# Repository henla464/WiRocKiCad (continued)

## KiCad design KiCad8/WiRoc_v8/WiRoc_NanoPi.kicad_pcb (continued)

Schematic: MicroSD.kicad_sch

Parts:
C30: 10uF/6.3V; C_0402_1005Metric
J3: Micro_SD_Card_Det1; TF-SMD_TF-018B-H15
R22: 33R; R_0402_1005Metric
R23, R24: 47K; R_0402_1005Metric
RV1, RV2, RV3, RV4, RV5, RV6, RV7, RV8: AVRL101A1R1NTB; R_0402_1005Metric

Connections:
GND: C30.1, J3.6 (VSS), J3.10 (SHIELD), RV1.2, RV2.2, RV3.2, RV4.2, RV5.2, RV6.2, RV7.2, RV8.2; also elsewhere on the board
unnamed: J3.5 (CLK), R22.2, RV6.1
SDC0-CLK: R22.1; also elsewhere on the board
SDC0-CMD: J3.3 (CMD), R23.1, RV1.1; also elsewhere on the board
SDC0-D0: J3.7 (DAT0), RV5.1; also elsewhere on the board
SDC0-D1: J3.8 (DAT1), RV4.1; also elsewhere on the board
SDC0-D2: J3.1 (DAT2), RV8.1; also elsewhere on the board
SDC0-D3: J3.2 (DAT3/CD), RV7.1; also elsewhere on the board
SDC0-DET: J3.9 (DET), R24.1, RV3.1; also elsewhere on the board
VDD_SYS_3.3V: C30.2, J3.4 (VDD), R23.2, R24.2, RV2.1; also elsewhere on the board

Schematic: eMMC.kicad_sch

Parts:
C32, C35, C80, C87, C88: 100nF; C_0402_1005Metric
C33, C34, C86: 1uF; C_0402_1005Metric
R26: 10K; R_0402_1005Metric
U14: KLM8G1WEPD-B031; MICRON_EMMC_153

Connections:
GND: C32.2, C33.2, C34.2, C35.2, C80.2, C86.2, C87.2, C88.2, U14.A6 (Vss), U14.C4 (Vss), U14.D4 (NC33), U14.E7 (Vss), U14.G5 (Vss), U14.H10 (Vss), U14.J5 (Vss), U14.K8 (Vss), U14.N2 (Vss), U14.N5 (Vss), U14.P2 (NC102), U14.P4 (Vss), U14.P6 (Vss), U14.P8 (NC103); also elsewhere on the board
unnamed: C32.1, C33.1, U14.C1 (NC19), U14.C2 (VDDI)
VDD_SYS_3.3V: C34.1, C35.1, C80.1, C86.1, C87.1, C88.1, R26.1, U14.C6 (VDD), U14.E6 (VDDF), U14.F5 (VDDF), U14.J10 (VDDF), U14.K9 (VDDF), U14.M4 (VDD), U14.N4 (VDD), U14.P3 (VDD), U14.P5 (VDD); also elsewhere on the board
eMMC-CLK: U14.M6 (CLK); also elsewhere on the board
eMMC-CMD: R26.2, U14.M5 (CMD); also elsewhere on the board
eMMC-D0: U14.A3 (DAT0); also elsewhere on the board
eMMC-D1: U14.A4 (DAT1); also elsewhere on the board
eMMC-D2: U14.A5 (DAT2); also elsewhere on the board
eMMC-D3: U14.B1 (NC10), U14.B2 (DAT3); also elsewhere on the board
eMMC-D4: U14.A2 (NC2), U14.B3 (DAT4); also elsewhere on the board
eMMC-D5: U14.B4 (DAT5), U14.C3 (NC20), U14.D1 (NC30), U14.D2 (NC31); also elsewhere on the board
eMMC-D6: U14.B5 (DAT6), U14.C5 (NC21); also elsewhere on the board
eMMC-D7: U14.A7 (RFU1), U14.B6 (DAT7); also elsewhere on the board
eMMC-RST: U14.K5 (RSTN); also elsewhere on the board

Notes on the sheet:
* Connected to simplify fanout from the eMMC chip

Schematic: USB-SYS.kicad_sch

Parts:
C31, C37, C39, C42, C43: 100nF; C_0402_1005Metric
C36: 1uF; C_0402_1005Metric
C38, C44: 4.7uF; C_0402_1005Metric
C40, C41: 18pF; C_0402_1005Metric
R27: 47K; R_0402_1005Metric
R28: 100K; R_0402_1005Metric
R29, R30, R31, R32: 10K; R_0402_1005Metric
R43: 0R; R_0402_1005Metric
U11: BGA-347_21x21_14.0x14.0mm
U13: SGM803-RXN3L; SOT-23-3
Y2: 24MHz/18pF; Crystal_SMD_2520-4Pin_2.5x2.0mm

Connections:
AP-RESET: C42.1, R29.2, U11.V6 (RESET), U13.2 (/RESET)
GND: C31.2, C36.1, C37.2, C38.2, C39.1, C40.1, C41.1, C42.2, C43.2, C44.2, U11.H8 (GND_TV), U11.M5 (HGND), U11.U3 (AGND), U13.1 (GND), Y2.2, Y2.4; also elsewhere on the board
GPIOL6/CPUX-VSET: U11.T4 (PL6/S_JTAG_DO/S_PL_EINT6); also elsewhere on the board
GPIOL8/PWR-STB: U11.T2 (PL8/S_PL_EINT8); also elsewhere on the board
GPIOL9/PWR-DRAM: U11.M6 (PL9/S_PL_EINT9); also elsewhere on the board
GPIOL10/PWR-LED: U11.V2 (PL10/S_PWM/S_PL_EINT10); also elsewhere on the board
LORARS: U11.U2 (PL11/S_CIR_RX/S_PL_EINT11); also elsewhere on the board
unnamed: R30.1, U11.R1 (PL3/S_UART_RX/S_PL_EINT3)
unnamed: R31.1, U11.N2 (PL4/S_JTAG_MS/S_PL_EINT4)
unnamed: C36.2, U11.W3 (MBIAS)
unnamed: R28.2, U11.AA5 (KEYADC)
unnamed: R27.2, U11.AA6 (NMI)
unnamed: R32.1, U11.W6 (UBOOT)
unnamed: C39.2, R43.1, U11.N3 (VCC_PLL)
unnamed: C38.1, U11.H11 (VDD_EFUSEBP)
USBHost-DM1: U11.A8 (USB_DM2); also elsewhere on the board
USBHost-DM2: U11.B9 (USB_DM3); also elsewhere on the board
USBHost-DP1: U11.A7 (USB_DP2); also elsewhere on the board
USBHost-DP2: U11.B8 (USB_DP3); also elsewhere on the board
VDD1V1-EPHY: U11.F8 (EPHY_VDD); also elsewhere on the board
VDD-CPUS: C44.1, U11.M4 (RTC_VIO); also elsewhere on the board
VDD_SYS_3.3V: C31.1, C37.1, C43.1, R27.1, R28.1, R29.1, R30.2, R31.2, R32.2, R43.2, U11.G7 (EPHY_VCC), U11.G9 (V33_TV), U11.G10 (VDD_EFUSE), U11.G11 (VCC-USB), U11.J6 (HVCC), U11.K6 (VCC_RTC), U11.V3 (AVCC), U13.3 (Vin); also elsewhere on the board
X24MI: C40.2, U11.K2 (X24MIN), Y2.1
X24MO: C41.2, U11.K1 (X24MOUT), Y2.3

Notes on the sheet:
ZeroPi uses a ferrite bead
Close to IC
Note: ZeroPi used 22pF capacitor and crystal has value "XTAL-2520-4P"
wifi clock,shouldn't be needed
WIFI (enable)

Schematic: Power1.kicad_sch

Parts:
C93, C95, C96: 10uF/6.3V; C_0402_1005Metric
C94: 22pF; C_0402_1005Metric
L6: DFE252010P-1R0M=P2; L_1008_2520Metric
Q1: L2N7002WT1G; SOT-323_SC-70
R50: 10K/1%; R_0402_1005Metric
R53: 12K/1%; R_0402_1005Metric
R54: 30K/1%; R_0402_1005Metric
R55: 10K; R_0402_1005Metric
U18: MP2143DJ; TSOT-23-8-Thinner-Pads

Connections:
GND: C93.2, C95.2, C96.2, Q1.2 (S), R53.1, U18.4 (GND), U18.6 (GND1); also elsewhere on the board
GPIOL6/CPUX-VSET: Q1.1 (G), R55.1; also elsewhere on the board
GPIOL8/PWR-STB: U18.8 (EN); also elsewhere on the board
unnamed: Q1.3 (D), R54.1
unnamed: C94.2, R50.1, R53.2, R54.2, U18.7 (FB)
unnamed: L6.1, U18.3 (SW)
VDD-CPUFB: C94.1, R50.2; also elsewhere on the board
VDD-CPUX: C95.1, C96.1, L6.2, U18.5 (OUT); also elsewhere on the board
VDD_5V: C93.1, U18.2 (VIN); also elsewhere on the board
VDD_SYS_3.3V: R55.2; also elsewhere on the board

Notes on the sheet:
GPIOL6/CPUX-VSET = 0, VDD-CPUX=1.1V GPIOL6/CPUX-VSET = 1, VDD-CPUX=1.3V
1.1V/1.3V/3A
Vfb=0.6V

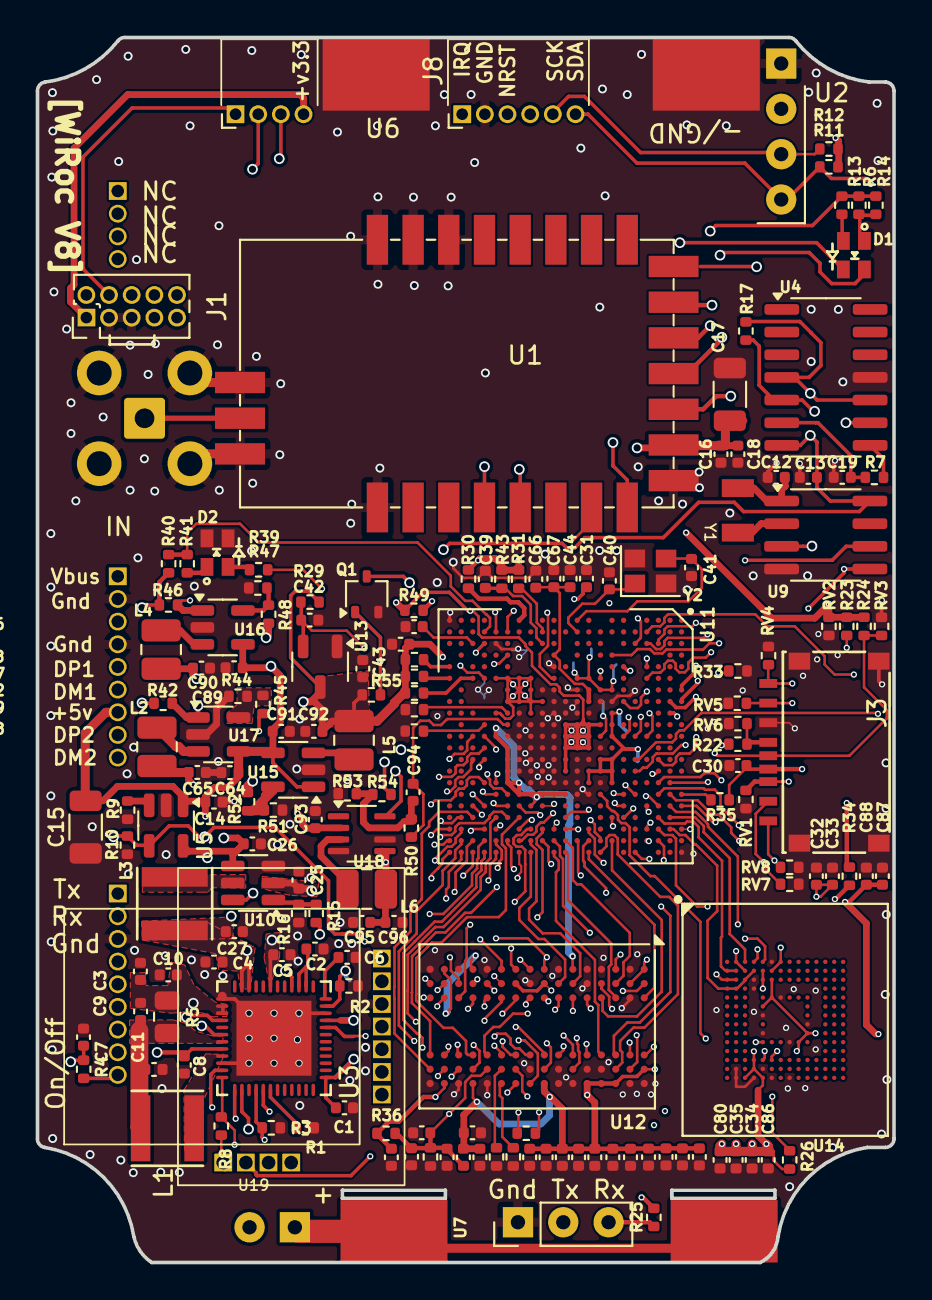
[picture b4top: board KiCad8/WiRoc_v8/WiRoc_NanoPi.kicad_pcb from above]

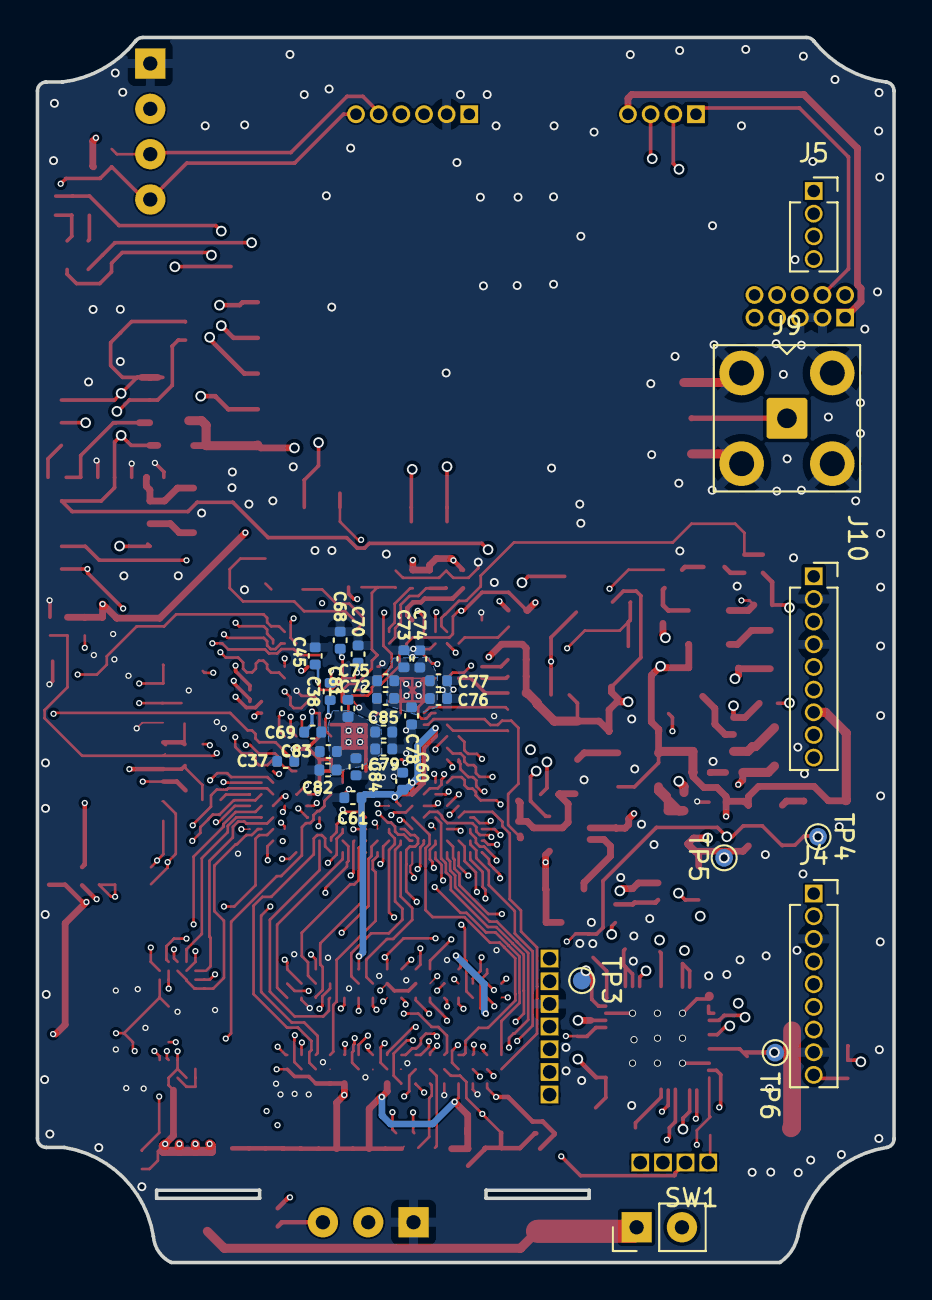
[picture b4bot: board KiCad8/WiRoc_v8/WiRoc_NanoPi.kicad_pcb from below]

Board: 6 copper layers, 48.0 x 68.7 mm, 197 parts (30 on the bottom side), 178 nets.

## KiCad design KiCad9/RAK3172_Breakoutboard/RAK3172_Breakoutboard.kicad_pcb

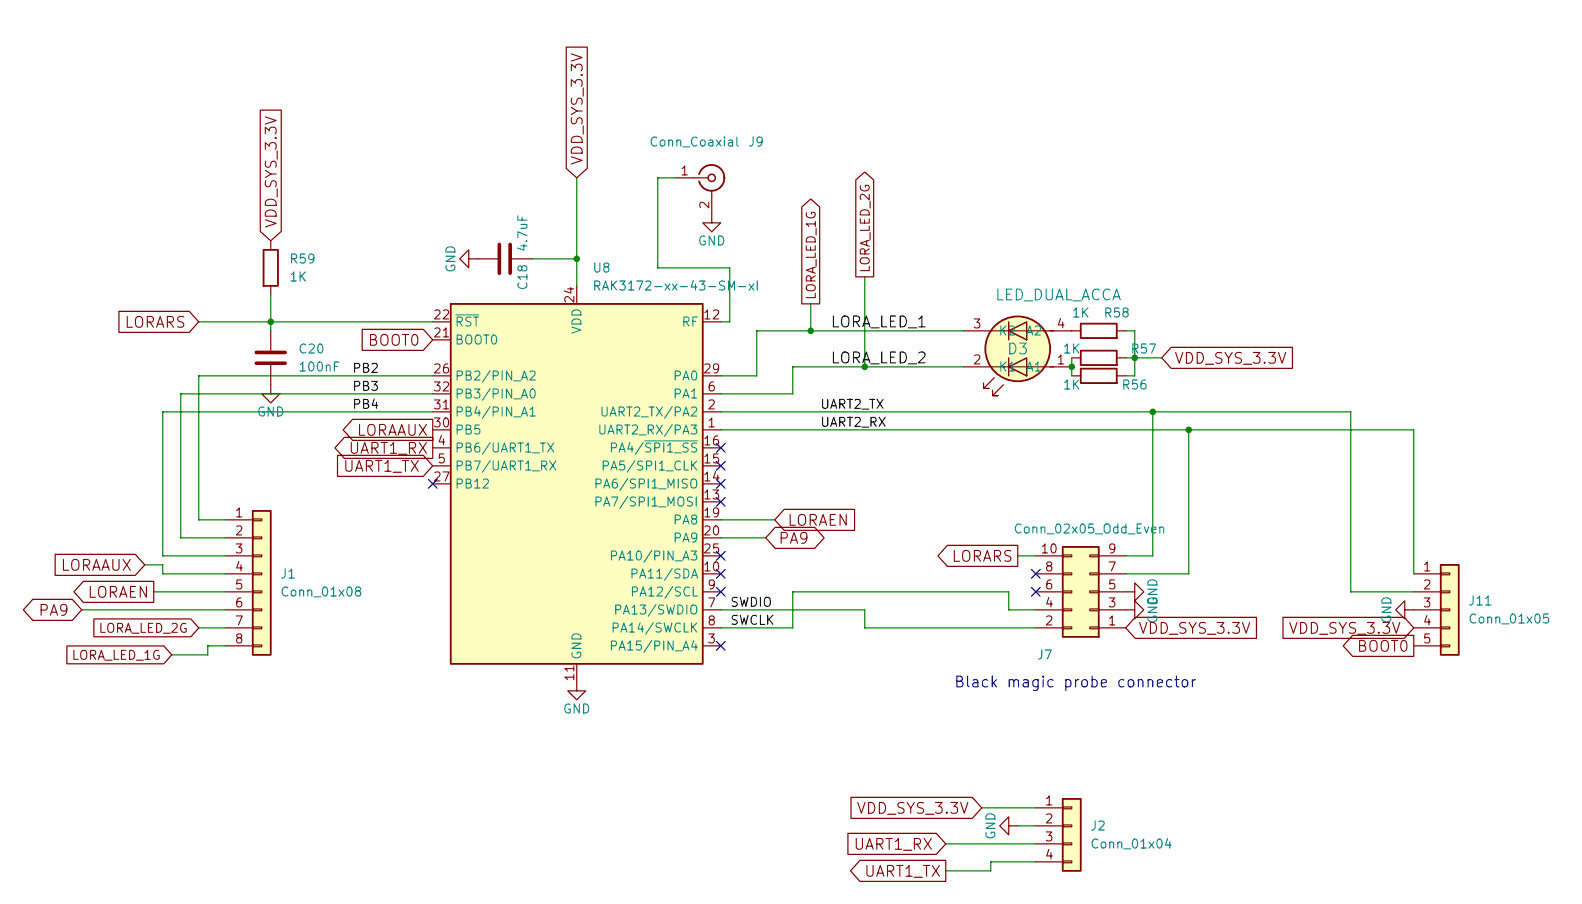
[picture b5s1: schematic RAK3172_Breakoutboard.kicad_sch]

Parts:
C18: 4.7uF; C_0603_1608Metric; ManufacturerPartNumber CL10A475KO8NNNC; LCSC Part # C19666
C20: 100nF; C_0402_1005Metric
D3: LED_DUAL_ACCA; LED_Dual_1.7_1.6; ManufacturerPartNumber HL-PCB-1617S9FH203BC; LCSC Part # C513363
J1: Conn_01x08; PinHeader_1x08_P2.54mm_Vertical
J2: Conn_01x04; PinHeader_1x04_P2.54mm_Vertical
J7: Conn_02x05_Odd_Even; PinHeader_2x05_P1.27mm_Vertical
J9: Conn_Coaxial; SMA_Amphenol_901-143_Horizontal
J11: Conn_01x05; PinHeader_1x05_P2.54mm_Vertical
R56, R57, R58: 1K; R_0603_1608Metric; ManufacturerPartNumber 0603WAJ0102T5E; LCSC Part # C21190
R59: 1K; R_0603_1608Metric
U8: RAK3172-xx-43-SM-xI; RAK3172

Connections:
/PB2: J1.1, U8.26 (PB2/PIN_A2)
/PB3: J1.2, U8.32 (PB3/PIN_A0)
/PB4: J1.3, U8.31 (PB4/PIN_A1)
/SWCLK: J7.4, U8.8 (PA14/SWCLK)
/SWDIO: J7.2, U8.7 (PA13/SWDIO)
/UART2_RX: J7.7, J11.1, U8.1 (UART2_RX/PA3)
/UART2_TX: J7.9, J11.2, U8.2 (UART2_TX/PA2)
BOOT0: J11.5, U8.21 (BOOT0)
GND: C18.2, C20.2, J2.2, J7.3, J7.5, J9.2 (Ext), J11.3, U8.11 (GND), U8.17 (GND), U8.18 (GND), U8.23 (GND), U8.28 (GND)
LORAAUX: J1.4, U8.30 (PB5)
LORAEN: J1.5, U8.19 (PA8)
LORARS: C20.1, J7.10, R59.2, U8.22 (~RST)
LORA_LED_1G: D3.3 (K2), J1.8, U8.29 (PA0)
LORA_LED_2G: D3.2 (K1), J1.7, U8.6 (PA1)
unnamed: D3.1 (A1), R56.1, R57.1
unnamed: D3.4 (A2), R58.1
unnamed: J9.1 (In), U8.12 (RF)
PA9: J1.6, U8.20 (PA9)
UART1_RX: J2.3, U8.4 (PB6/UART1_TX)
UART1_TX: J2.4, U8.5 (PB7/UART1_RX)
VDD_SYS_3.3V: C18.1, J2.1, J7.1, J11.4, R56.2, R57.2, R58.2, R59.1, U8.24 (VDD)

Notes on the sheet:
Black magic probe connector

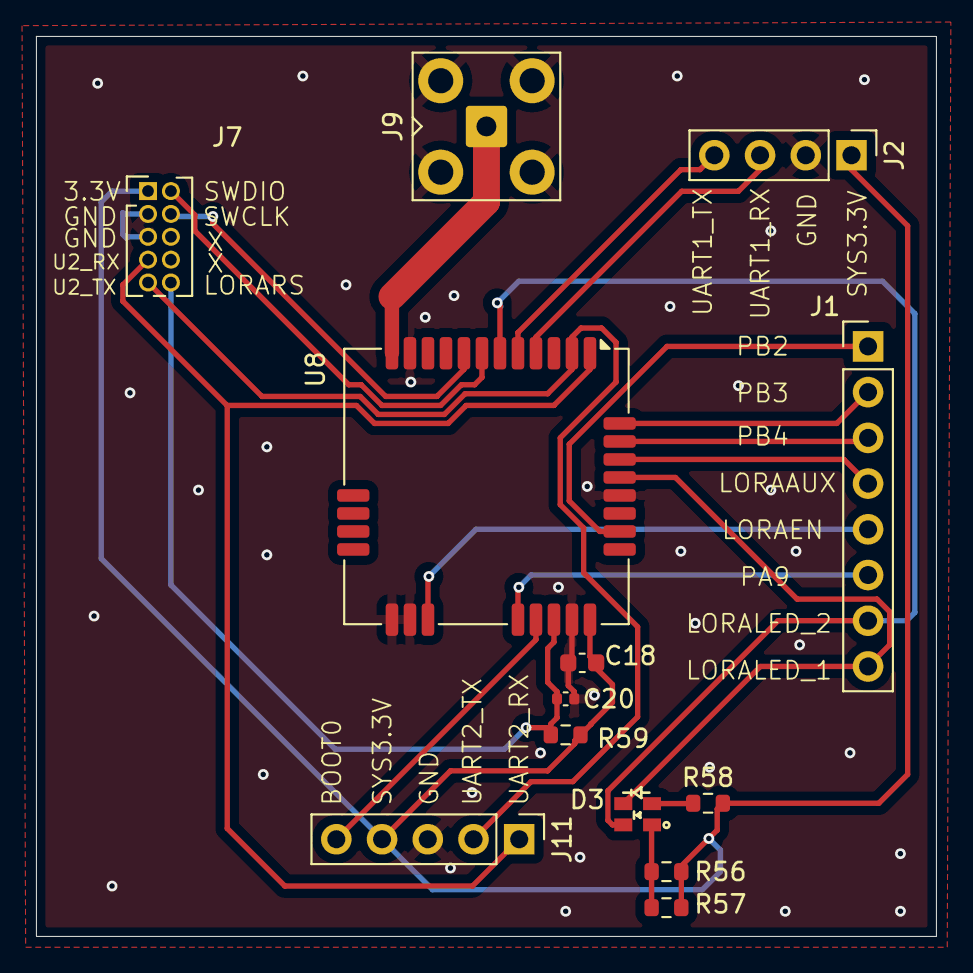
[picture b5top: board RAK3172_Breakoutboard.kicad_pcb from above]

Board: 2 copper layers, 50.0 x 50.0 mm, 13 parts (0 on the bottom side), 21 nets.

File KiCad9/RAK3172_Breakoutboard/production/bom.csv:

Designator,Footprint,Quantity,Value,LCSC Part #
C18,0603,1,4.7uF,C19666
C20,0402,1,100nF,
D3,LED_Dual_1.7_1.6,1,LED_DUAL_ACCA,C513363
J1,PinHeader_1x08_P2.54mm_Vertical,1,Conn_01x08,
J11,PinHeader_1x05_P2.54mm_Vertical,1,Conn_01x05,
J2,PinHeader_1x04_P2.54mm_Vertical,1,Conn_01x04,
J7,PinHeader_2x05_P1.27mm_Vertical,1,Conn_02x05_Odd_Even,
"R56, R57, R58",0603,3,1K,C21190
R59,0603,1,1K,
U8,RAK3172,1,RAK3172-xx-43-SM-xI,
